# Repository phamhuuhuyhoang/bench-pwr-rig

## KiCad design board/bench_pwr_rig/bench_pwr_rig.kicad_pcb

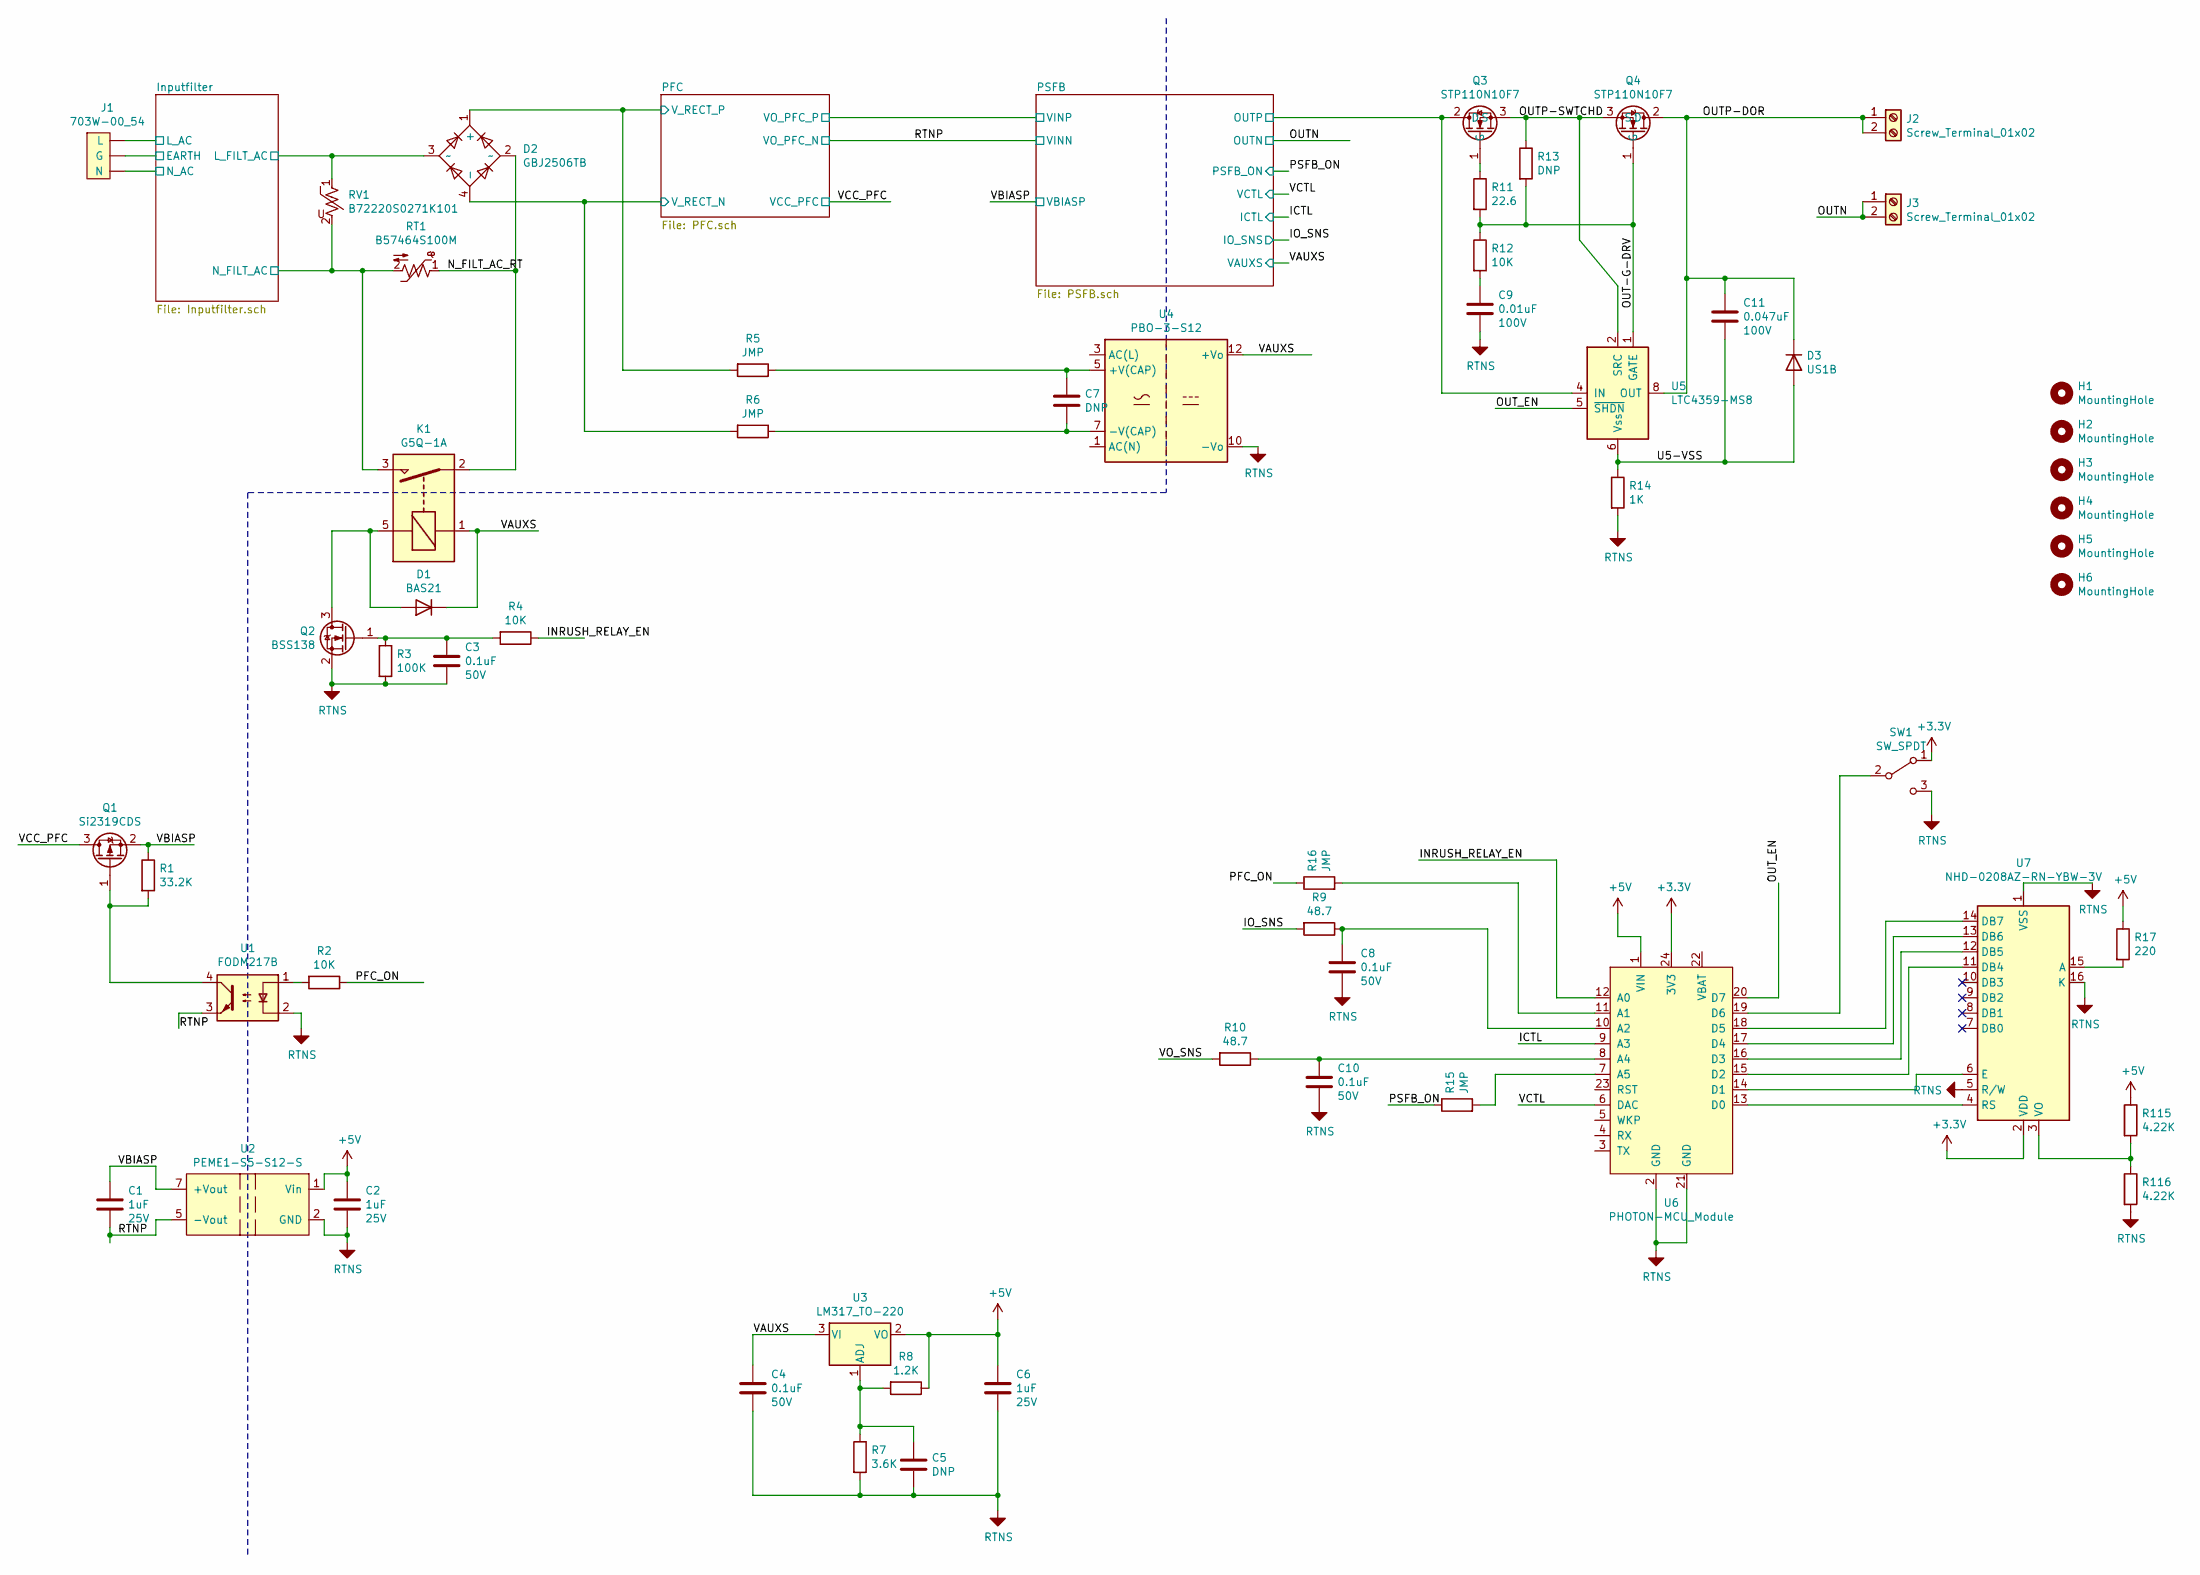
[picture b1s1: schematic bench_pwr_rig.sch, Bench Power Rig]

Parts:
C1, C2, C6: C1608X7R1E105K080AB; C_0603_1608Metric_Pad1.05x0.95mm_HandSolder; Voltage 25V
C3, C4, C8, C10: C1608X7R1H104K; C_0603_1608Metric_Pad1.05x0.95mm_HandSolder; Voltage 50V
C5: DNP; C_0603_1608Metric_Pad1.05x0.95mm_HandSolder
C7: DNP; C_1206_3216Metric
C9: CL21B103KCANNNC; C_0805_2012Metric_Pad1.15x1.40mm_HandSolder; Voltage 100V
C11: CL21B473KCFNNNE; C_0805_2012Metric_Pad1.15x1.40mm_HandSolder; Voltage 100V
D1: BAS21; SOT-23
D2: GBJ2506TB; Diode_Bridge_30.0x4.6x20.0mm_P10.0mm_P7.5mm
D3: US1B; D_SMA
H1, H2, H3, H4, H5, H6: MountingHole; MountingHole_4.3mm_M4
J1: 703W-00_54; 703W-00
J2, J3: Screw_Terminal_01x02; TerminalBlock_Phoenix_MKDS-1,5-2-5.08_1x02_P5.08mm_Horizont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
K1: G5Q-1A; Relay_SPST_Omron-G5Q-1A
Q1: Si2319CDS; SOT-23
Q2: BSS138; SOT-23
Q3, Q4: STP110N10F7; TO-220-3_Vertical
R1: CRCW060333K2FKEA; R_0603_1608Metric_Pad1.05x0.95mm_HandSolder
R2, R4, R12: CRCW060310K0FKEA; R_0603_1608Metric_Pad1.05x0.95mm_HandSolder
R3: 0603WAF1003T5E; R_0603_1608Metric_Pad1.05x0.95mm_HandSolder
R5, R6, R15, R16: JMP; R_0603_1608Metric_Pad1.05x0.95mm_HandSolder
R7: 0603WAF3601T5E; R_0603_1608Metric_Pad1.05x0.95mm_HandSolder
R8: 0603WAF1201T5E; R_0603_1608Metric_Pad1.05x0.95mm_HandSolder
R9, R10: 0603WAF4872T5E; R_0603_1608Metric_Pad1.05x0.95mm_HandSolder
R11: 0603WAF226JT5E; R_0603_1608Metric_Pad1.05x0.95mm_HandSolder
R13: DNP; R_0603_1608Metric_Pad1.05x0.95mm_HandSolder
R14: 0805W8F1001T5E; R_0805_2012Metric_Pad1.15x1.40mm_HandSolder
R17: 0603WAF2200T5E; R_0603_1608Metric_Pad1.05x0.95mm_HandSolder
R115, R116: 0603WAF4221T5E; R_0603_1608Metric_Pad1.05x0.95mm_HandSolder
RT1: B57464S100M; C_Disc_D16.0mm_W5.0mm_P7.50mm
RV1: B72220S0271K101; C_Disc_D16.0mm_W5.0mm_P10.00mm
SW1: SW_SPDT; SW_SPDT_CK-JS102011SAQN
U1: FODM217B; SOP-4_4.4x2.6mm_P1.27mm
U2: PEME1-S5-S12-S; Converter_DCDC_Murata_MGJ2DxxxxxxSC_THT
U3: LM317_TO-220; TO-220-3_Vertical
U4: PBO-3-S12; Converter_ACDC_CUI_PBO-3-Sxx_THT_Vertical
U5: LTC4359-MS8; MSOP-8_3x3mm_P0.65mm
U6: PHOTON-MCU_Module; photon_tht
U7: NHD-0208AZ-RN-YBW-3V; PinHeader_2x08_P2.54mm_Vertical

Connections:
+3V3: SW1.1 (A), U6.24 (3V3), U7.2 (VDD)
+5V: C2.1, C6.1, R8.1, R17.1, R115.1, U2.1 (Vin), U3.2 (VO), U6.1 (VIN); also elsewhere on the board
+12V: C4.1, D1.3 (K), K1.1, U3.3 (VI), U4.12 (+Vo); also elsewhere on the board
/ICTL: U6.9 (A3); also elsewhere on the board
/INRUSH_RELAY_EN: R4.1, U6.12 (A0)
/IO_SNS: R9.2; also elsewhere on the board
/Inputfilter/L_AC: J1.1 (L); also elsewhere on the board
/Inputfilter/L_FILT_AC: D2.3 (~~), RV1.1; also elsewhere on the board
/Inputfilter/N_AC: J1.3 (N); also elsewhere on the board
/Inputfilter/N_FILT_AC: K1.3, RT1.2, RV1.2; also elsewhere on the board
/N_FILT_AC_RT: D2.2 (~~), K1.2, RT1.1
/OUT-G-DRV: Q4.1 (G), R11.2, R12.1, R13.2, U5.1 (GATE)
/OUTN: J3.1, J3.2; also elsewhere on the board
/OUTP-DOR: C11.1, D3.1 (K), J2.1, J2.2, Q4.2 (D), U5.8 (OUT)
/OUTP-SWTCHD: Q3.3 (S), Q4.3 (S), R13.1, U5.2 (SRC)
/OUT_EN: U5.5 (~SHDN), U6.20 (D7)
/PFC/V_RECT_N: D2.4 (-), R6.2; also elsewhere on the board
/PFC/V_RECT_P: D2.1 (+), R5.2; also elsewhere on the board
/PFC_ON: R2.1, R16.1
/PSFB/OUTP: Q3.2 (D), U5.4 (IN); also elsewhere on the board
/PSFB_ON: R15.1; also elsewhere on the board
/RTNP: C1.2, U1.3, U2.5 (-Vout); also elsewhere on the board
/U5-VSS: C11.2, D3.2 (A), R14.1, U5.6 (Vss)
/VBIASP: C1.1, Q1.2 (S), R1.1, U2.7 (+Vout); also elsewhere on the board
/VCC_PFC: Q1.3 (D); also elsewhere on the board
/VCTL: U6.6 (DAC); also elsewhere on the board
/VO_SNS: R10.2
Earth: J1.2 (G); also elsewhere on the board
GND: C2.2, C3.2, C4.2, C5.2, C6.2, C8.2, C9.2, C10.2, Q2.2 (S), R3.2, R7.2, R14.2, R116.2, SW1.3 (C), U1.2, U2.2 (GND), U4.10 (-Vo), U6.2 (GND), U6.21 (GND), U7.1 (VSS), U7.5 (R/W), U7.16 (K); also elsewhere on the board
unnamed: C3.1, Q2.1 (G), R3.1, R4.2
unnamed: C5.1, R7.1, R8.2, U3.1 (ADJ)
unnamed: C7.1, R5.1, U4.5 (+V(CAP))
unnamed: C7.2, R6.1, U4.7 (-V(CAP))
unnamed: C8.1, R9.1, U6.10 (A2)
unnamed: C9.1, R12.2
unnamed: C10.1, R10.1, U6.8 (A4)
unnamed: D1.1 (A), K1.5, Q2.3 (D)
unnamed: Q1.1 (G), R1.2, U1.4
unnamed: Q3.1 (G), R11.1
unnamed: R2.2, U1.1
unnamed: R15.2, U6.7 (A5)
unnamed: R16.2, U6.11 (A1)
unnamed: R17.2, U7.15 (A)
unnamed: R115.2, R116.1, U7.3 (VO)
unnamed: SW1.2 (B), U6.19 (D6)
unnamed: U6.13 (D0), U7.4 (RS)
unnamed: U6.14 (D1), U7.6 (E)
unnamed: U6.15 (D2), U7.11 (DB4)
unnamed: U6.16 (D3), U7.12 (DB5)
unnamed: U6.17 (D4), U7.13 (DB6)
unnamed: U6.18 (D5), U7.14 (DB7)

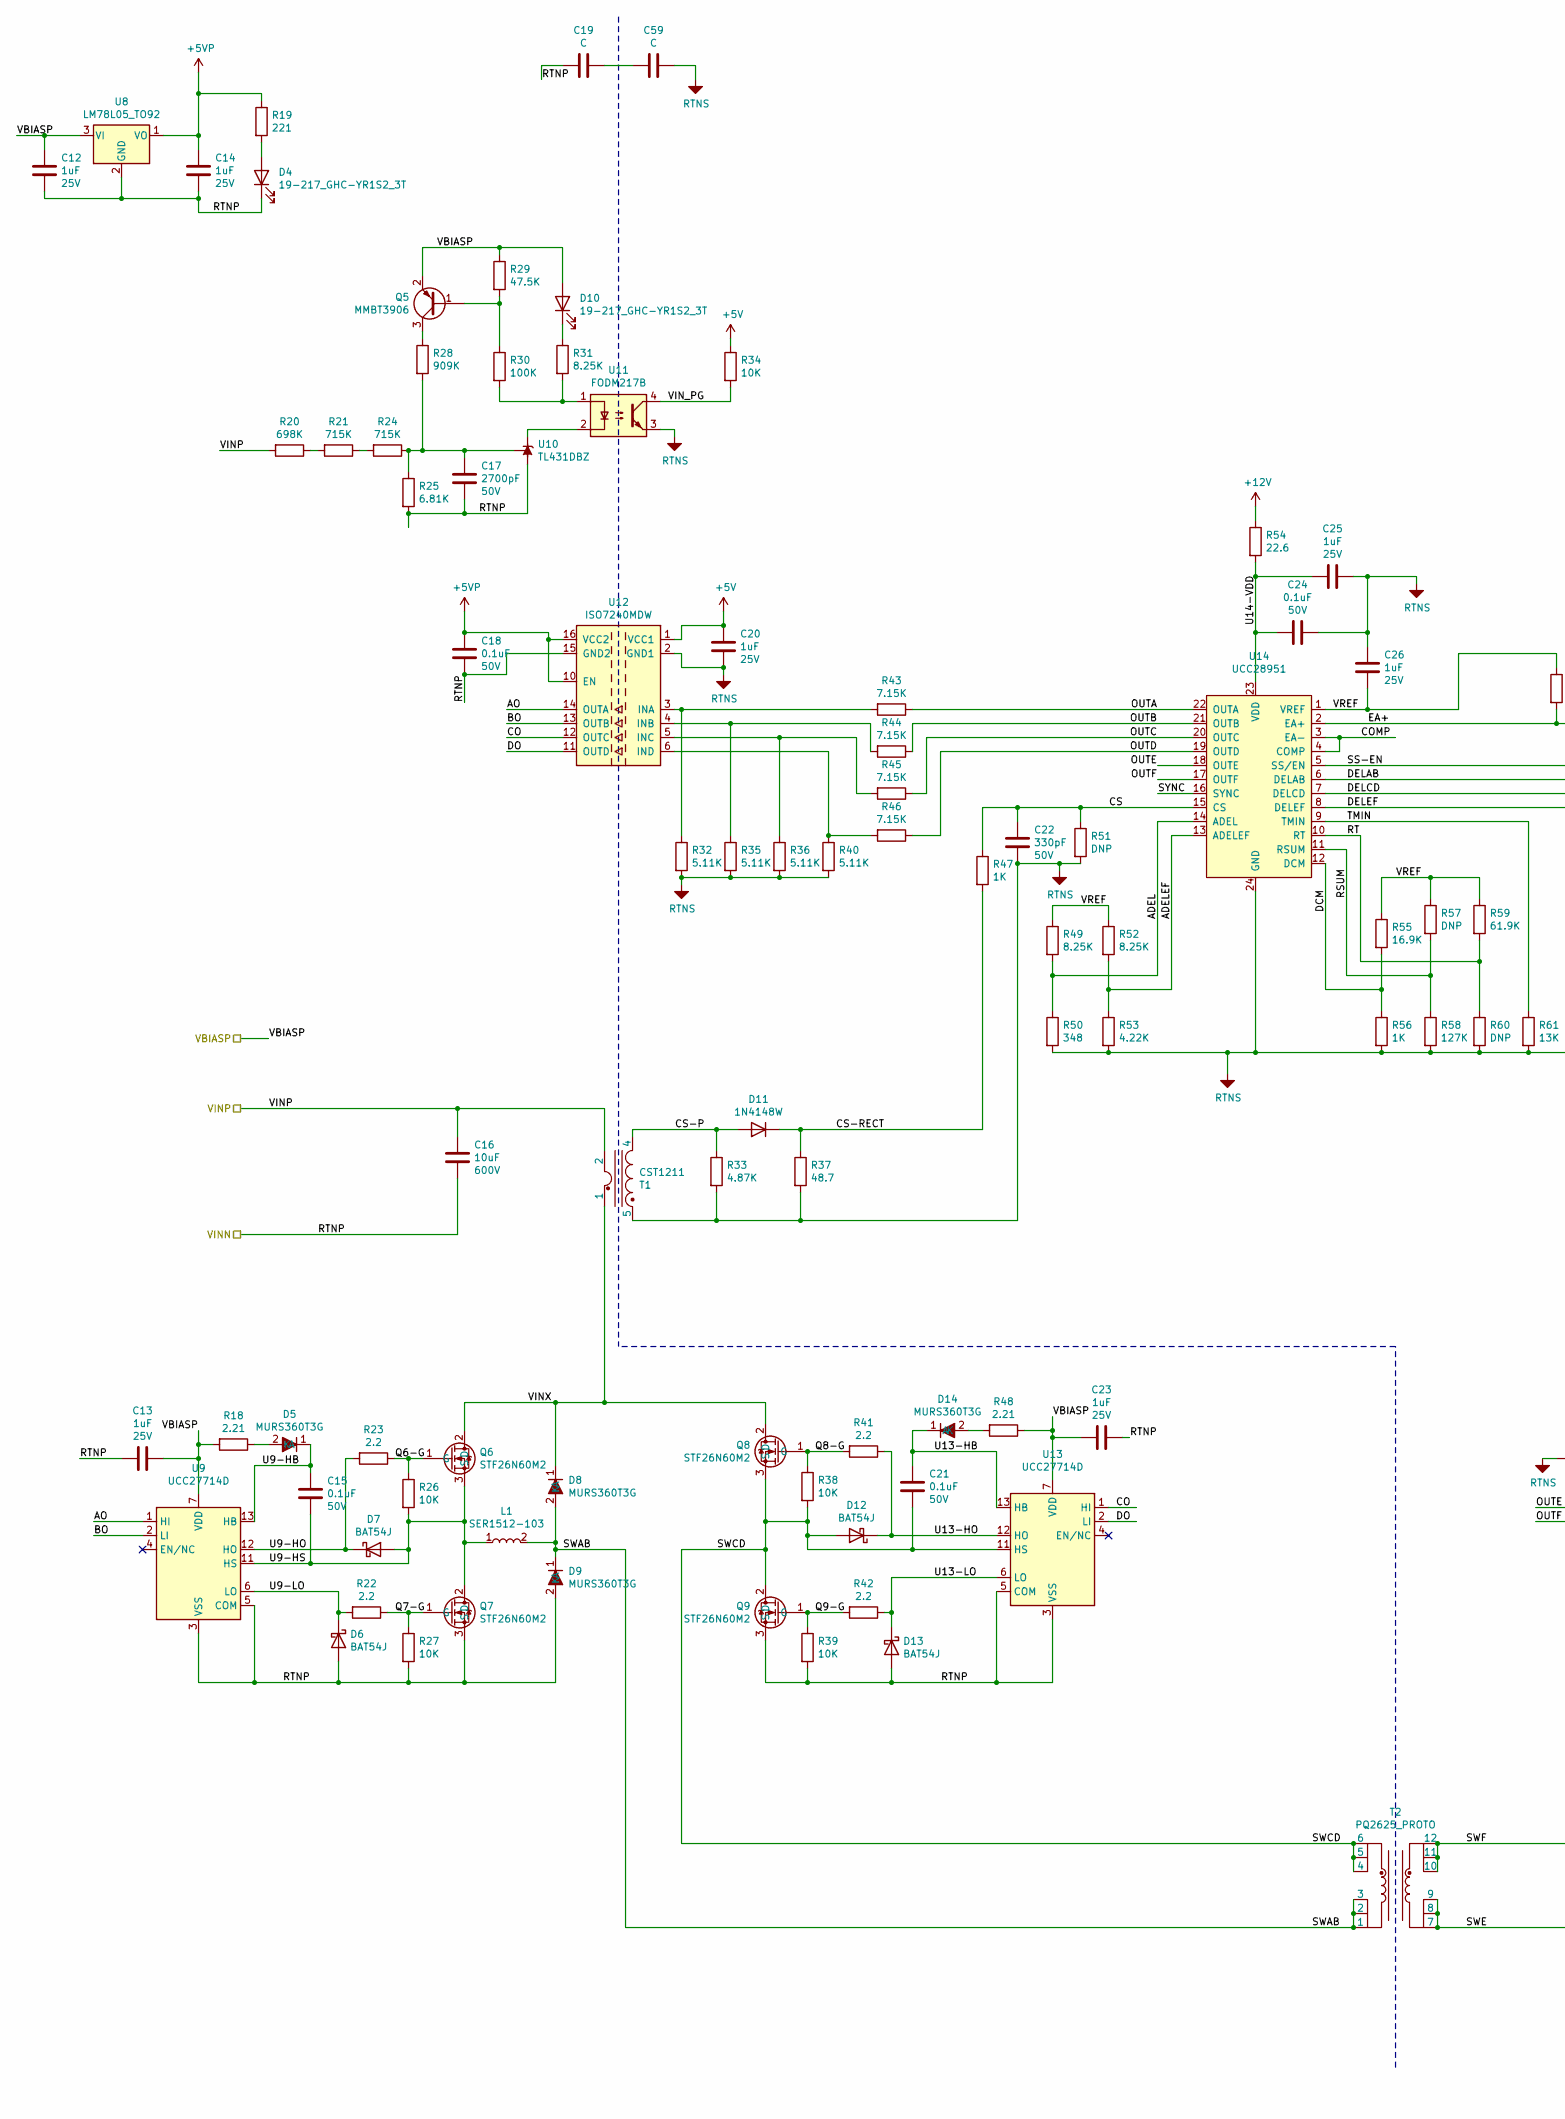
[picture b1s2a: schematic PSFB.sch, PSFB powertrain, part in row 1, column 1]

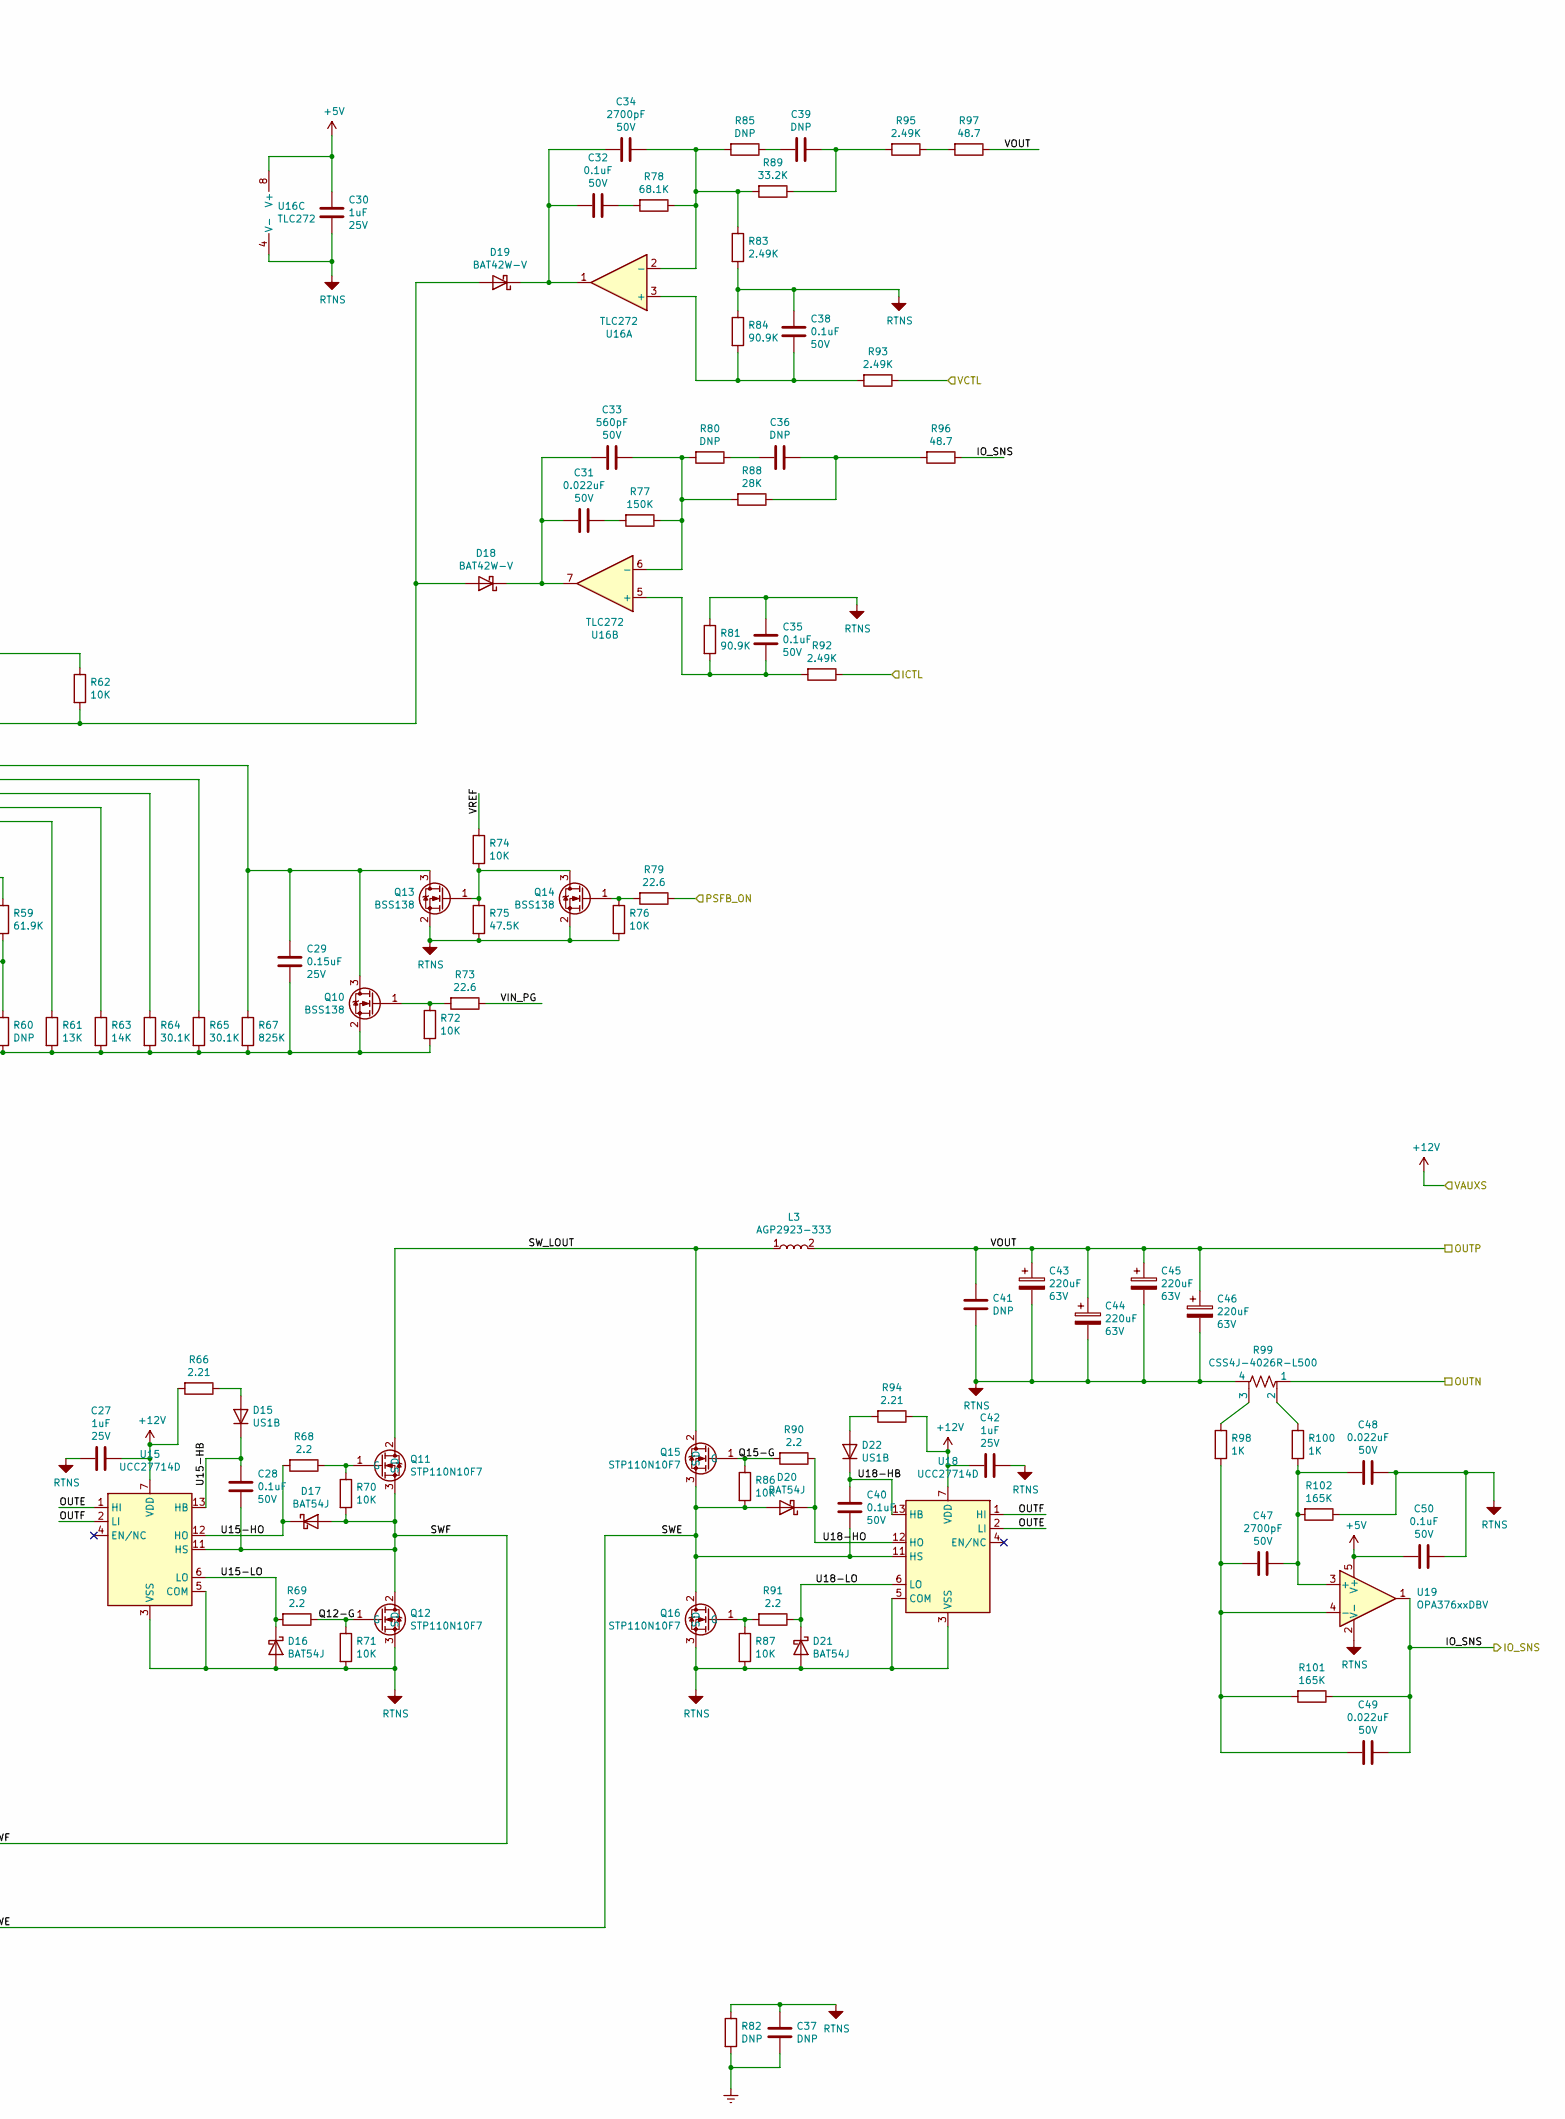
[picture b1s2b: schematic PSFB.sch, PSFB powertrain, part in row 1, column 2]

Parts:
C12, C13, C14, C20, C23, C25, C26, C27, C30, C42: C1608X7R1E105K080AB; C_0603_1608Metric_Pad1.05x0.95mm_HandSolder; Voltage 25V
C15, C18, C21, C24, C28, C32, C35, C38, C40, C50: C1608X7R1H104K; C_0603_1608Metric_Pad1.05x0.95mm_HandSolder; Voltage 50V
C16: C4AEHBU5100A11J; C_Rect_L33.0mm_W20.0mm_P27.50mm_MKS4; Voltage 600V
C17, C34, C47: C1608C0G1H272J; C_0603_1608Metric_Pad1.05x0.95mm_HandSolder; Voltage 50V
C19, C59: C; C_Disc_D9.0mm_W5.0mm_P10.00mm
C22: CL10C331JB8NNNC; C_0603_1608Metric_Pad1.05x0.95mm_HandSolder; Voltage 50V
C29: CL10B154KA8NNNC; C_0603_1608Metric_Pad1.05x0.95mm_HandSolder; Voltage 25V
C31, C48, C49: CL10B223KB8NNNC; C_0603_1608Metric_Pad1.05x0.95mm_HandSolder; Voltage 50V
C33: C1608C0G1H561J; C_0603_1608Metric_Pad1.05x0.95mm_HandSolder; Voltage 50V
C36, C39: DNP; C_0603_1608Metric_Pad1.05x0.95mm_HandSolder
C37, C41: DNP; C_1206_3216Metric
C43, C44, C45, C46: EEU-EB1J221; CP_Radial_D10.0mm_P5.00mm; Voltage 63V
D4, D10: 19-217_GHC-YR1S2_3T; LED_0603_1608Metric_Pad1.05x0.95mm_HandSolder
D5, D8, D9, D14: MURS360T3G; D_SMC_Handsoldering
D6, D7, D12, D13, D16, D17, D20, D21: BAT54J; D_SOD-323F
D11: 1N4148W; D_SOD-123
D15, D22: US1B; D_SMA
D18, D19: BAT42W-V; D_SOD-123
L1: SER1512-103; L_Coilcraft_SER1512
L3: AGP2923-333; L_Coilcraft_AGP2923
Q5: MMBT3906; SOT-23
Q6, Q7, Q8, Q9: STF26N60M2; TO-220-3_Vertical_Stag
Q10, Q13, Q14: BSS138; SOT-23
Q11, Q12, Q15, Q16: STP110N10F7; TO-220-3_Vertical
R18, R48, R66, R94: CRCW08052R21FKEA; R_0805_2012Metric_Pad1.15x1.40mm_HandSolder
R19: CRCW0603221RFKEA; R_0603_1608Metric_Pad1.05x0.95mm_HandSolder
R20: 1206W4F6983T5E; R_1206_3216Metric_Pad1.42x1.75mm_HandSolder
R21, R24: 1206W4F7153T5E; R_1206_3216Metric_Pad1.42x1.75mm_HandSolder
R22, R23, R41, R42, R68, R69, R90, R91: 0603WAF220KT5E; R_0603_1608Metric_Pad1.05x0.95mm_HandSolder
R25: 0603WAF6811T5E; R_0603_1608Metric_Pad1.05x0.95mm_HandSolder
R26, R27, R34, R38, R39, R62, R70, R71, R72, R74, R76, R86, R87: CRCW060310K0FKEA; R_0603_1608Metric_Pad1.05x0.95mm_HandSolder
R28: 0603WAF9093T5E; R_0603_1608Metric_Pad1.05x0.95mm_HandSolder
R29, R75: 0603WAF4752T5E; R_0603_1608Metric_Pad1.05x0.95mm_HandSolder
R30: 0603WAF1003T5E; R_0603_1608Metric_Pad1.05x0.95mm_HandSolder
R31, R49, R52: 0603WAF8251T5E; R_0603_1608Metric_Pad1.05x0.95mm_HandSolder
R32, R35, R36, R40: 0603WAF5111T5E; R_0603_1608Metric_Pad1.05x0.95mm_HandSolder
R33: 0603WAF4871T5E; R_0603_1608Metric_Pad1.05x0.95mm_HandSolder
R37, R96, R97: 0603WAF4872T5E; R_0603_1608Metric_Pad1.05x0.95mm_HandSolder
R43, R44, R45, R46: 0603WAF7151T5E; R_0603_1608Metric_Pad1.05x0.95mm_HandSolder
R47, R56, R98, R100: 0603WAF1001T5E; R_0603_1608Metric_Pad1.05x0.95mm_HandSolder
R50: 0603WAF3480T5E; R_0603_1608Metric_Pad1.05x0.95mm_HandSolder
R51, R57, R60, R80, R85: DNP; R_0603_1608Metric_Pad1.05x0.95mm_HandSolder
R53: 0603WAF4221T5E; R_0603_1608Metric_Pad1.05x0.95mm_HandSolder
R54, R73, R79: 0603WAF226JT5E; R_0603_1608Metric_Pad1.05x0.95mm_HandSolder
R55: 0603WAF1692T5E; R_0603_1608Metric_Pad1.05x0.95mm_HandSolder
R58: 0603WAF1273T5E; R_0603_1608Metric_Pad1.05x0.95mm_HandSolder
R59: 0603WAF6192T5E; R_0603_1608Metric_Pad1.05x0.95mm_HandSolder
R61: CRCW060313K0FKEA; R_0603_1608Metric_Pad1.05x0.95mm_HandSolder
R63: 0603WAF1402T5E; R_0603_1608Metric_Pad1.05x0.95mm_HandSolder
R64, R65: 0603WAF3012T5E; R_0603_1608Metric_Pad1.05x0.95mm_HandSolder
R67: 0603WAF8253T5E; R_0603_1608Metric_Pad1.05x0.95mm_HandSolder
R77: 0603WAF1503T5E; R_0603_1608Metric_Pad1.05x0.95mm_HandSolder
R78: 0603WAF6812T5E; R_0603_1608Metric_Pad1.05x0.95mm_HandSolder
R81, R84: 0603WAF9092T5E; R_0603_1608Metric_Pad1.05x0.95mm_HandSolder
R82: DNP; R_1206_3216Metric
R83, R92, R93, R95: 0603WAF2491T5E; R_0603_1608Metric_Pad1.05x0.95mm_HandSolder
R88: 0603WAF2802T5E; R_0603_1608Metric_Pad1.05x0.95mm_HandSolder
R89: CRCW060333K2FKEA; R_0603_1608Metric_Pad1.05x0.95mm_HandSolder
R99: CSS4J-4026R-L500; R_Shunt_Bourns_CSS4J_4026
R101, R102: 0603WAF1653T5E; R_0603_1608Metric_Pad1.05x0.95mm_HandSolder
T1: CST1211; Transformer_Coilcraft_CST1211
T2: PQ2625_PROTO; CPV-PQ26-25-1S-12PD-Z
U8: LM78L05_TO92; TO-92_Inline
U9, U13, U15, U18: UCC27714D; SOIC-14_3.9x8.7mm_P1.27mm
U10: TL431DBZ; SOT-23
U11: FODM217B; SOP-4_4.4x2.6mm_P1.27mm
U12: ISO7240MDW; SOIC-16W_7.5x10.3mm_P1.27mm
U14: UCC28951; TSSOP-24_4.4x7.8mm_P0.65mm
U16: TLC272; SOIC-8_3.9x4.9mm_P1.27mm
U19: OPA376xxDBV; SOT-23-5

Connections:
+5V: C20.1, C30.1, C50.2, R34.1, U12.1 (VCC1), U16.8 (V+), U19.5 (V+); also elsewhere on the board
+5VP: C14.1, C18.1, R19.1, U8.1 (VO), U12.10 (EN), U12.16 (VCC2)
+12V: C27.1, C42.2, R54.1, R66.2, R94.1, U15.7 (VDD), U18.7 (VDD); also elsewhere on the board
/ICTL: R92.1; also elsewhere on the board
/IO_SNS: C49.2, R96.1, R101.1, U19.1; also elsewhere on the board
/OUTN: R99.1; also elsewhere on the board
/PSFB/ADEL: R49.2, R50.1, U14.14 (ADEL)
/PSFB/ADELEF: R52.2, R53.1, U14.13 (ADELEF)
/PSFB/AO: U9.1 (HI), U12.14 (OUTA)
/PSFB/BO: U9.2 (LI), U12.13 (OUTB)
/PSFB/CO: U12.12 (OUTC), U13.1 (HI)
/PSFB/COMP: U14.3 (EA-), U14.4 (COMP)
/PSFB/CS: C22.1, R47.1, R51.1, U14.15 (CS)
/PSFB/CS-P: D11.2 (A), R33.1, T1.4
/PSFB/CS-RECT: D11.1 (K), R37.1, R47.2
/PSFB/DCM: R55.2, R56.1, U14.12 (DCM)
/PSFB/DELAB: R65.1, U14.6 (DELAB)
/PSFB/DELCD: R64.1, U14.7 (DELCD)
/PSFB/DELEF: R63.1, U14.8 (DELEF)
/PSFB/DO: U12.11 (OUTD), U13.2 (LI)
/PSFB/EA+: D18.2 (A), D19.2 (A), R62.2, U14.2 (EA+)
/PSFB/OUTA: R43.1, U14.22 (OUTA)
/PSFB/OUTB: R44.1, U14.21 (OUTB)
/PSFB/OUTC: R45.1, U14.20 (OUTC)
/PSFB/OUTD: R46.1, U14.19 (OUTD)
/PSFB/OUTE: U14.18 (OUTE), U15.1 (HI), U18.2 (LI)
/PSFB/OUTF: U14.17 (OUTF), U15.2 (LI), U18.1 (HI)
/PSFB/OUTP: C41.1, C43.1, C44.1, C45.1, C46.1, L3.2, R97.1; also elsewhere on the board
/PSFB/Q6-G: Q6.1 (G), R23.1, R26.1
/PSFB/Q7-G: Q7.1 (G), R22.1, R27.1
/PSFB/Q8-G: Q8.1 (G), R38.1, R41.2
/PSFB/Q9-G: Q9.1 (G), R39.1, R42.2
/PSFB/Q12-G: Q12.1 (G), R69.1, R71.1
/PSFB/Q15-G: Q15.1 (G), R86.1, R90.2
/PSFB/RSUM: R57.2, R58.1, U14.11 (RSUM)
/PSFB/RT: R59.2, R60.1, U14.10 (RT)
/PSFB/SS-EN: C29.1, Q10.3 (D), Q13.3 (D), R67.1, U14.5 (SS/EN)
/PSFB/SWAB: D8.2 (A), D9.1 (K), L1.2, T2.1, T2.2, T2.3
/PSFB/SWCD: C21.2, D12.2 (A), Q8.3 (S), Q9.2 (D), R38.2, T2.4, T2.5, T2.6, U13.11 (HS)
/PSFB/SWE: C40.2, D20.2 (A), Q15.3 (S), Q16.2 (D), R86.2, T2.7, T2.8, T2.9, U18.11 (HS)
/PSFB/SWF: C28.2, D17.2 (A), Q11.3 (S), Q12.2 (D), R70.2, T2.10, T2.11, T2.12, U15.11 (HS)
/PSFB/SW_LOUT: L3.1, Q11.2 (D), Q15.2 (D)
/PSFB/SYNC: U14.16 (SYNC)
/PSFB/TMIN: R61.1, U14.9 (TMIN)
/PSFB/U9-HB: C15.1, D5.1 (K), U9.13 (HB)
/PSFB/U9-HO: D7.1 (K), R23.2, U9.12 (HO)
/PSFB/U9-HS: C15.2, D7.2 (A), L1.1, Q6.3 (S), Q7.2 (D), R26.2, U9.11 (HS)
/PSFB/U9-LO: D6.1 (K), R22.2, U9.6 (LO)
/PSFB/U13-HB: C21.1, D14.1 (K), U13.13 (HB)
/PSFB/U13-HO: D12.1 (K), R41.1, U13.12 (HO)
/PSFB/U13-LO: D13.1 (K), R42.1, U13.6 (LO)
/PSFB/U14-VDD: C24.2, C25.2, R54.2, U14.23 (VDD)
/PSFB/U15-HB: C28.1, D15.1 (K), U15.13 (HB)
/PSFB/U15-HO: D17.1 (K), R68.2, U15.12 (HO)
/PSFB/U15-LO: D16.1 (K), R69.2, U15.6 (LO)
/PSFB/U18-HB: C40.1, D22.1 (K), U18.13 (HB)
/PSFB/U18-HO: D20.1 (K), R90.1, U18.12 (HO)
/PSFB/U18-LO: D21.1 (K), R91.1, U18.6 (LO)
/PSFB/VINP: C16.1, R20.2, T1.2; also elsewhere on the board
/PSFB/VINX: D8.1 (K), Q6.2 (D), Q8.2 (D), T1.1
/PSFB/VIN_PG: R34.2, R73.1, U11.4
/PSFB/VREF: C26.2, R49.1, R52.1, R55.1, R57.1, R59.1, R62.1, R74.1, U14.1 (VREF)
/PSFB_ON: R79.1; also elsewhere on the board
/RTNP: C12.2, C13.2, C14.2, C16.2, C17.2, C18.2, C19.2, C23.1, D4.1 (K), D6.2 (A), D9.2 (A), D13.2 (A), Q7.3 (S), Q9.3 (S), R25.2, R27.2, R39.2, U8.2 (GND), U9.3 (VSS), U9.5 (COM), U10.3 (A), U12.9 (GND2), U12.15 (GND2), U13.3 (VSS), U13.5 (COM); also elsewhere on the board
/VBIASP: C12.1, C13.1, C23.2, D10.2 (A), Q5.2 (E), R18.2, R29.1, R48.1, U8.3 (VI), U9.7 (VDD), U13.7 (VDD); also elsewhere on the board
/VCTL: R93.1; also elsewhere on the board
Earth: C37.2, R82.2; also elsewhere on the board
GND: C20.2, C22.2, C24.1, C25.1, C26.1, C27.2, C29.2, C30.2, C35.1, C37.1, C38.1, C41.2, C42.1, C43.2, C44.2, C45.2, C46.2, C48.1, C50.1, C59.1, D16.2 (A), D21.2 (A), Q10.2 (S), Q12.3 (S), Q13.2 (S), Q14.2 (S), Q16.3 (S), R32.2, R33.2, R35.2, R36.2, R37.2, R40.2, R50.2, R51.2, R53.2, R56.2, R58.2, R60.2, R61.2, R63.2, R64.2, R65.2, R67.2, R71.2, R72.2, R75.2, R76.2, R81.1, R82.1, R83.2, R84.1, R87.2, R99.4, R102.1, T1.5, U11.3, U12.2 (GND1), U12.8 (GND1), U14.24 (GND), U15.3 (VSS), U15.5 (COM), U16.4 (V-), U18.3 (VSS), U18.5 (COM), U19.2 (V-); also elsewhere on the board
unnamed: C17.1, R24.1, R25.1, R28.2, U10.2 (REF)
unnamed: C19.1, C59.2
unnamed: C31.1, R77.2
unnamed: C31.2, C33.2, D18.1 (K), U16.7
unnamed: C32.1, R78.2
unnamed: C32.2, C34.2, D19.1 (K), U16.1
unnamed: C33.1, R77.1, R80.2, R88.2, U16.6 (-)
unnamed: C34.1, R78.1, R83.1, R85.2, R89.2, U16.2 (-)
unnamed: C35.2, R81.2, R92.2, U16.5 (+)
unnamed: C36.1, R88.1, R96.2
unnamed: C36.2, R80.1
unnamed: C38.2, R84.2, R93.2, U16.3 (+)
unnamed: C39.1, R89.1, R95.2
unnamed: C39.2, R85.1
unnamed: C47.1, C48.2, R100.2, R102.2, U19.3 (+)
unnamed: C47.2, C49.1, R98.2, R101.2, U19.4 (-)
unnamed: D4.2 (A), R19.2
unnamed: D5.2 (A), R18.1
unnamed: D10.1 (K), R31.1
unnamed: D14.2 (A), R48.2
unnamed: D15.2 (A), R66.1
unnamed: D22.2 (A), R94.2
unnamed: Q5.1 (B), R29.2, R30.1
unnamed: Q5.3 (C), R28.1
unnamed: Q10.1 (G), R72.1, R73.2
unnamed: Q11.1 (G), R68.1, R70.1
unnamed: Q13.1 (G), Q14.3 (D), R74.2, R75.1
unnamed: Q14.1 (G), R76.1, R79.2
unnamed: Q16.1 (G), R87.1, R91.2
unnamed: R20.1, R21.2
unnamed: R21.1, R24.2
unnamed: R30.2, R31.2, U11.1
unnamed: R32.1, R43.2, U12.3 (INA)
unnamed: R35.1, R44.2, U12.4 (INB)
unnamed: R36.1, R45.2, U12.5 (INC)
unnamed: R40.1, R46.2, U12.6 (IND)
unnamed: R95.1, R97.2
unnamed: R98.1, R99.3
unnamed: R99.2, R100.1
unnamed: U10.1 (K), U11.2

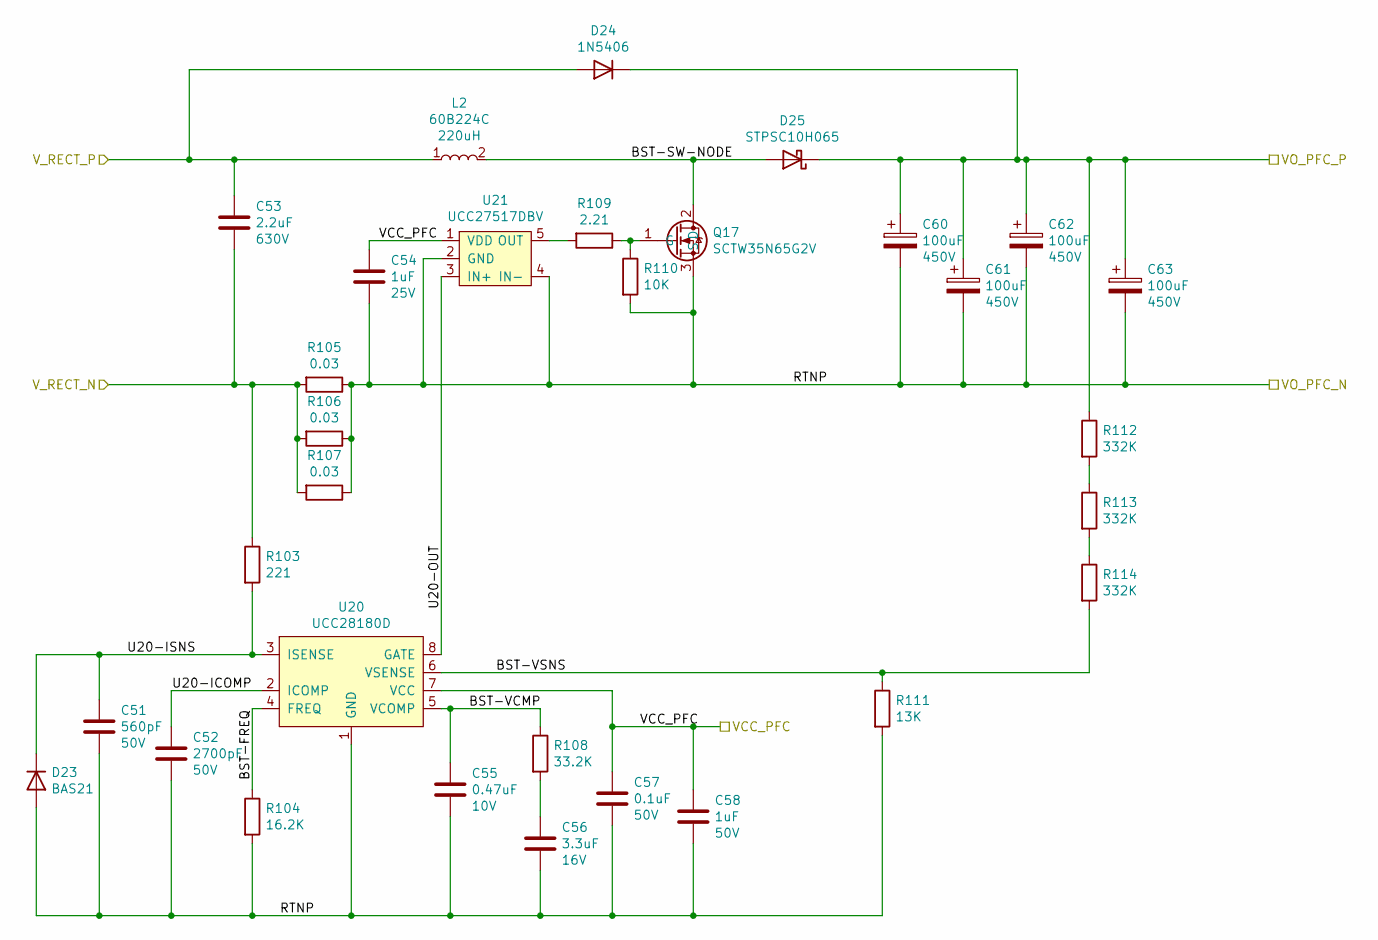
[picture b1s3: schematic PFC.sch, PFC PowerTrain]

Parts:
C51: C1608C0G1H561J; C_0603_1608Metric_Pad1.05x0.95mm_HandSolder; Voltage 50V
C52: C1608C0G1H272J; C_0603_1608Metric_Pad1.05x0.95mm_HandSolder; Voltage 50V
C53: ECW-FA2J225J; C_Rect_L26.0mm_W16.3mm_P22.50mm; Voltage 630V
C54: C1608X7R1E105K080AB; C_0603_1608Metric_Pad1.05x0.95mm_HandSolder; Voltage 25V
C55: C1608X5R1A474K; C_0603_1608Metric_Pad1.05x0.95mm_HandSolder; Voltage 10V
C56: CL31B335KOHNNNE; C_1206_3216Metric_Pad1.42x1.75mm_HandSolder; Voltage 16V
C57: CC0805KRX7R9BB104; C_0805_2012Metric_Pad1.15x1.40mm_HandSolder; Voltage 50V
C58: CL21B105KBFNNNE; C_0805_2012Metric_Pad1.15x1.40mm_HandSolder; Voltage 50V
C60, C61, C62, C63: EKXG451ELL101MM40S; CP_Radial_D18.0mm_P7.50mm; Voltage 450V
D23: BAS21; SOT-23
D24: 1N5406; D_DO-201AD_P15.24mm_Horizontal
D25: STPSC10H065; TO-220-2_Vertical
L2: 60B224C; L_Murata_6000B_Handsoldering
Q17: SCTW35N65G2V; TO-247-3_Vertical
R103: CRCW0603221RFKEA; R_0603_1608Metric_Pad1.05x0.95mm_HandSolder
R104: CRCW060316K2FKEA; R_0603_1608Metric_Pad1.05x0.95mm_HandSolder
R105, R106, R107: CSRN2512FK30L0; R_2512_6332Metric_Pad1.52x3.35mm_HandSolder
R108: CRCW060333K2FKEA; R_0603_1608Metric_Pad1.05x0.95mm_HandSolder
R109: CRCW08052R21FKEA; R_0805_2012Metric_Pad1.15x1.40mm_HandSolder
R110: CRCW060310K0FKEA; R_0603_1608Metric_Pad1.05x0.95mm_HandSolder
R111: CRCW060313K0FKEA; R_0603_1608Metric_Pad1.05x0.95mm_HandSolder
R112, R113, R114: CRCW1206332KFKEA; R_1206_3216Metric_Pad1.42x1.75mm_HandSolder
U20: UCC28180D; SOIC-8_3.9x4.9mm_P1.27mm
U21: UCC27517DBV; SOT-23-5_HandSoldering

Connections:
/PFC/BST-FREQ: R104.1, U20.4 (FREQ)
/PFC/BST-SW-NODE: D25.2 (A), L2.2, Q17.2 (D)
/PFC/BST-VCMP: C55.1, R108.1, U20.5 (VCOMP)
/PFC/BST-VSNS: R111.1, R114.2, U20.6 (VSENSE)
/PFC/U20-ICOMP: C52.1, U20.2 (ICOMP)
/PFC/U20-ISNS: C51.1, D23.3 (K), R103.2, U20.3 (ISENSE)
/PFC/U20-OUT: U20.8 (GATE), U21.3 (IN+)
/PFC/V_RECT_N: C53.2, R103.1, R105.2, R106.2, R107.2; also elsewhere on the board
/PFC/V_RECT_P: C53.1, D24.2 (A), L2.1; also elsewhere on the board
/PSFB/VINP: C60.1, C61.1, C62.1, C63.1, D24.1 (K), D25.1 (K), R112.1; also elsewhere on the board
/RTNP: C51.2, C52.2, C54.2, C55.2, C56.2, C57.2, C58.2, C60.2, C61.2, C62.2, C63.2, D23.1 (A), Q17.3 (S), R104.2, R105.1, R106.1, R107.1, R110.2, R111.2, U20.1 (GND), U21.2 (GND), U21.4 (IN-); also elsewhere on the board
/VCC_PFC: C54.1, C57.1, C58.1, U20.7 (VCC), U21.1 (VDD); also elsewhere on the board
unnamed: C56.1, R108.2
unnamed: Q17.1 (G), R109.1, R110.1
unnamed: R109.2, U21.5 (OUT)
unnamed: R112.2, R113.1
unnamed: R113.2, R114.1

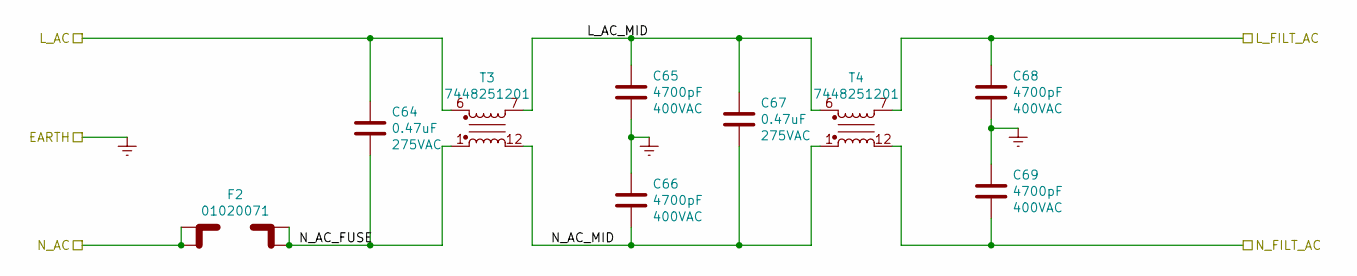
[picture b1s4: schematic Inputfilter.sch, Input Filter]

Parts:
C64, C67: ECQ-U2A474ML; C_Rect_L26.5mm_W8.5mm_P22.50mm_MKS4; Voltage 275VAC
C65, C66, C68, C69: C961U472MYWDBA7317; C_Disc_D14.5mm_W5.0mm_P10.00mm; Voltage 400VAC
F2: 01020071; Fuseholder_Littelfuse_0.25inD_1.25inL
T3, T4: 7448251201; Choke_Wurth_7448251201

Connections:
/Inputfilter/L_AC: C64.1, T3.6; also elsewhere on the board
/Inputfilter/L_AC_MID: C65.1, C67.1, T3.7, T4.6
/Inputfilter/L_FILT_AC: C68.1, T4.7; also elsewhere on the board
/Inputfilter/N_AC: F2.1, F2.2; also elsewhere on the board
/Inputfilter/N_AC_FUSE: C64.2, F2.3, F2.4, T3.1
/Inputfilter/N_AC_MID: C66.2, C67.2, T3.12, T4.1
/Inputfilter/N_FILT_AC: C69.2, T4.12; also elsewhere on the board
Earth: C65.2, C66.1, C68.2, C69.1; also elsewhere on the board
